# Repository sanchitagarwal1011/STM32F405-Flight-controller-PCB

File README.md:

# STM32F405 Flight Controller PCB

A custom flight controller PCB designed in KiCad 10 using the STM32F405 microcontroller.

This project focuses on embedded systems, PCB design, and drone electronics.

## Project Overview

The board includes:

- STM32F405 microcontroller
- ICM-20602 6-axis IMU
- BMP280 barometric pressure sensor
- AMS1117-3.3 voltage regulator
- USB interface
- ESC signal connections
- RC receiver connections
- Reset and boot controls
- Power filtering and decoupling capacitors

## Tools Used

- KiCad 10
- Embedded C
- Git
- GitHub

## PCB Design

### Schematic

### PCB Layout

### 3D View

## Design Features

- STM32F405-based flight controller
- Dedicated ground plane
- Separate power and signal routing
- Decoupling capacitors near IC power pins
- IMU placed close to the microcontroller
- Power filtering for sensitive components
- Design-rule checking using KiCad

## Project Status

- [x] Schematic design
- [x] Component selection
- [x] Footprint assignment
- [x] PCB placement
- [x] PCB routing
- [x] Ground-zone filling
- [x] Design-rule checking
- [x] Gerber generation
- [ ] PCB manufacturing
- [ ] Hardware testing

## Reference

This project is inspired by PCB design learning material from Phil’s Lab.

## Disclaimer

This is a learning and development project. The board has not yet been flight-tested and should not be used in a real drone.

## Author

Sanchit Agarwal

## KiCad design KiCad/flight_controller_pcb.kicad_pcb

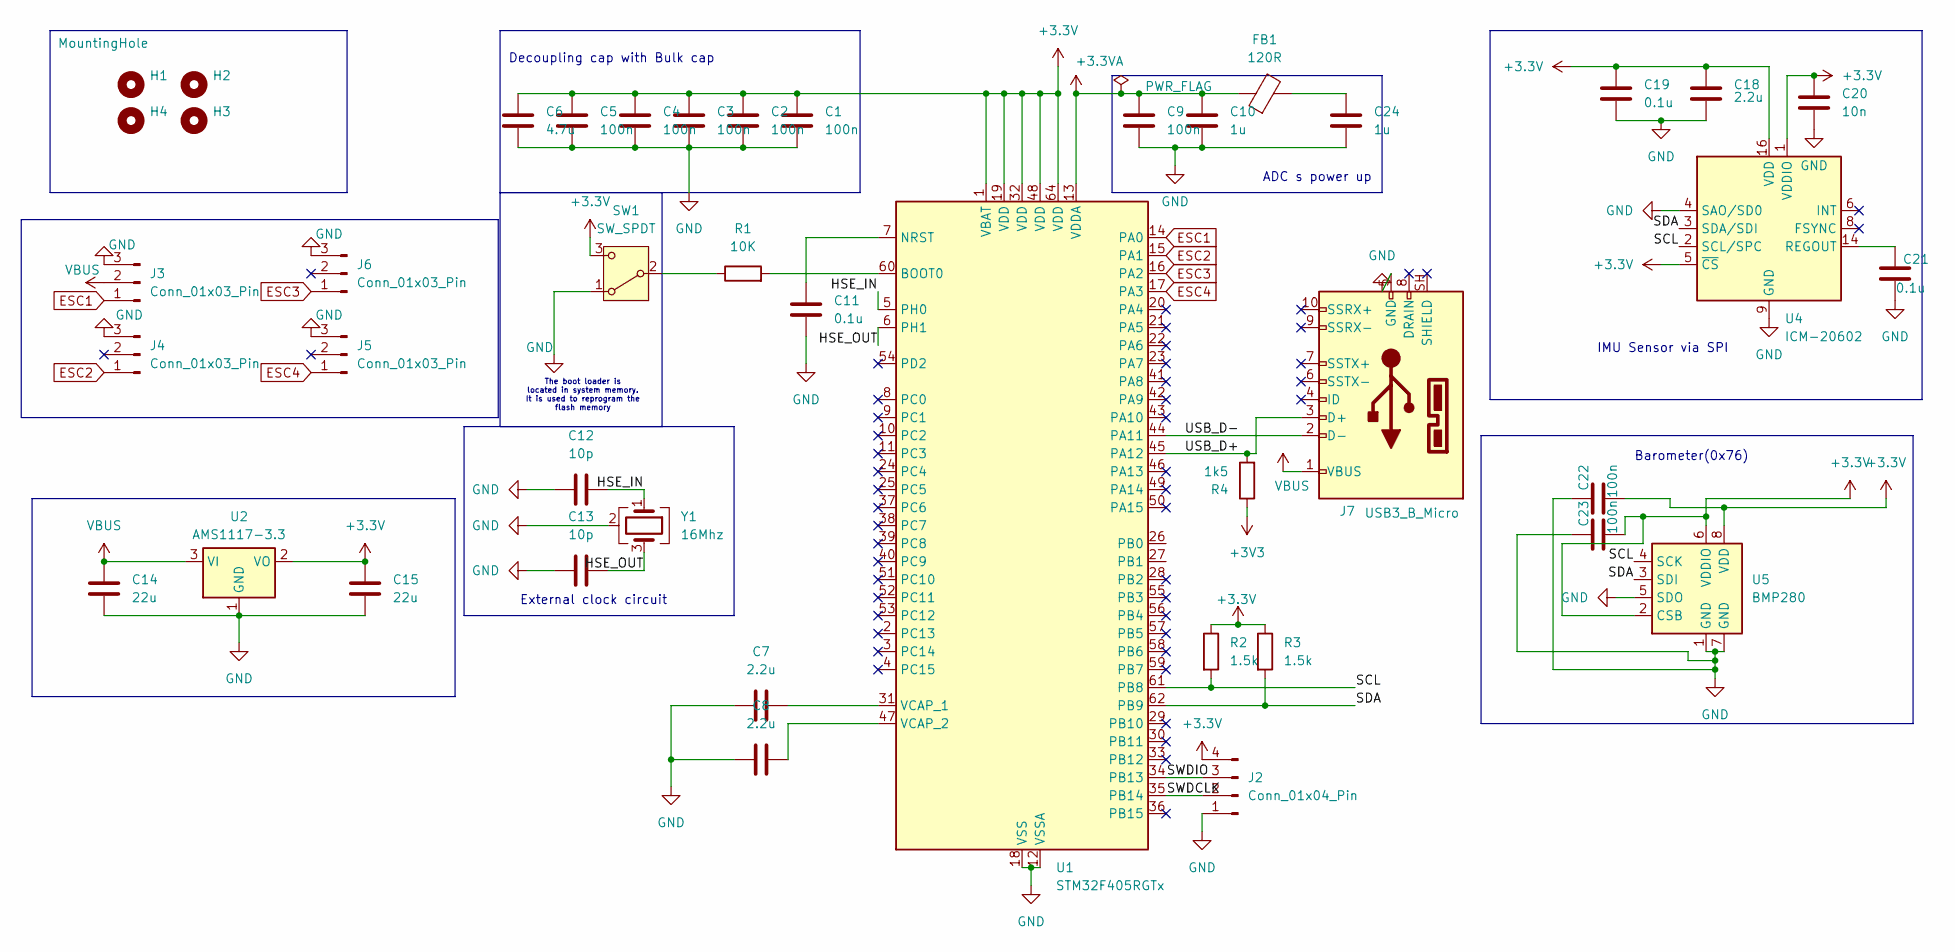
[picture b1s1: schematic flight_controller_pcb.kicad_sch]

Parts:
C1, C2, C3, C4, C5, C9, C22, C23: 100n; C_0603_1608Metric
C6: 4.7u; C_0603_1608Metric
C7, C8: 2.2u; C_0805_2012Metric
C10, C24: 1u; C_0603_1608Metric
C11, C19, C21: 0.1u; C_0603_1608Metric
C12, C13: 10p; C_0603_1608Metric
C14, C15: 22u; C_0805_2012Metric
C18: 2.2u; C_0603_1608Metric
C20: 10n; C_0603_1608Metric
FB1: 120R; L_0603_1608Metric
H1, H2, H3, H4: MountingHole; MountingHole_2.1mm
J2: Conn_01x04_Pin; PinHeader_1x04_P2.54mm_Vertical
J3, J4, J5, J6: Conn_01x03_Pin; PinHeader_1x03_P2.54mm_Vertical
J7: USB3_B_Micro; USB_Micro-B_Wuerth_629105150521
R1: 10K; R_0805_2012Metric
R2, R3: 1.5k; R_0805_2012Metric
R4: 1k5; R_0402_1005Metric
SW1: SW_SPDT; SW_SPDT_PCM12
U1: STM32F405RGTx; LQFP-64_10x10mm_P0.5mm
U2: AMS1117-3.3; SOT-223-3_TabPin2
U4: ICM-20602; LGA-16_3x3mm_P0.5mm_LayoutBorder3x5y
U5: BMP280; Bosch_LGA-8_2x2.5mm_P0.65mm_ClockwisePinNumbering
Y1: 16Mhz; Crystal_SMD_3225-4Pin_3.2x2.5mm

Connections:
+3.3V: C1.1, C2.1, C3.1, C4.1, C5.1, C6.1, C15.1, C18.1, C19.1, C20.1, C22.2, C23.2, J2.4, R2.1, R3.1, SW1.3 (C), U1.1 (VBAT), U1.19 (VDD), U1.32 (VDD), U1.48 (VDD), U1.64 (VDD), U2.2 (VO), U4.1 (VDDIO), U4.5 (~CS), U4.16 (VDD), U5.2 (CSB), U5.6 (VDDIO), U5.8 (VDD)
+3.3VA: C9.1, C10.1, FB1.1, U1.13 (VDDA)
+3V3: R4.1
/HSE_IN: C12.1, U1.5 (PH0), Y1.1
/HSE_OUT: C13.1, U1.6 (PH1), Y1.3
/SCL: R2.2, U1.61 (PB8), U4.2 (SCL/SPC), U5.4 (SCK)
/SDA: R3.2, U1.62 (PB9), U4.3 (SDA/SDI), U5.3 (SDI)
/SWDCLK: J2.2, U1.35 (PB14)
/SWDIO: J2.3, U1.34 (PB13)
/USB_D+: J7.3 (D+), R4.2, U1.45 (PA12)
/USB_D-: J7.2 (D-), U1.44 (PA11)
ESC1: J3.1, U1.14 (PA0)
ESC2: J4.1, U1.15 (PA1)
ESC3: J6.1, U1.16 (PA2)
ESC4: J5.1, U1.17 (PA3)
GND: C1.2, C2.2, C3.2, C4.2, C5.2, C6.2, C7.2, C8.1, C9.2, C10.2, C11.2, C12.2, C13.2, C14.2, C15.2, C18.2, C19.2, C20.2, C21.2, C22.1, C23.1, C24.2, J2.1, J3.3, J4.3, J5.3, J6.3, J7.5 (GND), SW1.1 (A), U1.12 (VSSA), U1.18 (VSS), U1.63 (VSS), U2.1 (GND), U4.4 (SAO/SD0), U4.9 (GND), U4.10 (GND), U4.11 (GND), U4.12 (GND), U4.13 (GND), U4.15 (GND), U5.1 (GND), U5.5 (SDO), U5.7 (GND), Y1.2 (G), Y1.4 (G)
unnamed: C24.1, FB1.2
unnamed: R1.1, SW1.2 (B)
unnamed: R1.2, U1.60 (BOOT0)
unnamed: C11.1, U1.7 (NRST)
unnamed: C7.1, U1.31 (VCAP_1)
unnamed: C8.2, U1.47 (VCAP_2)
unnamed: C21.1, U4.14 (REGOUT)
VBUS: C14.1, J3.2, J7.1 (VBUS), U2.3 (VI)

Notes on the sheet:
ADC s power up
External clock circuit
Barometer(0x76)
IMU Sensor via SPI
Decoupling cap with Bulk cap
The boot loader is located in system memory. It is used to reprogram the flash memory

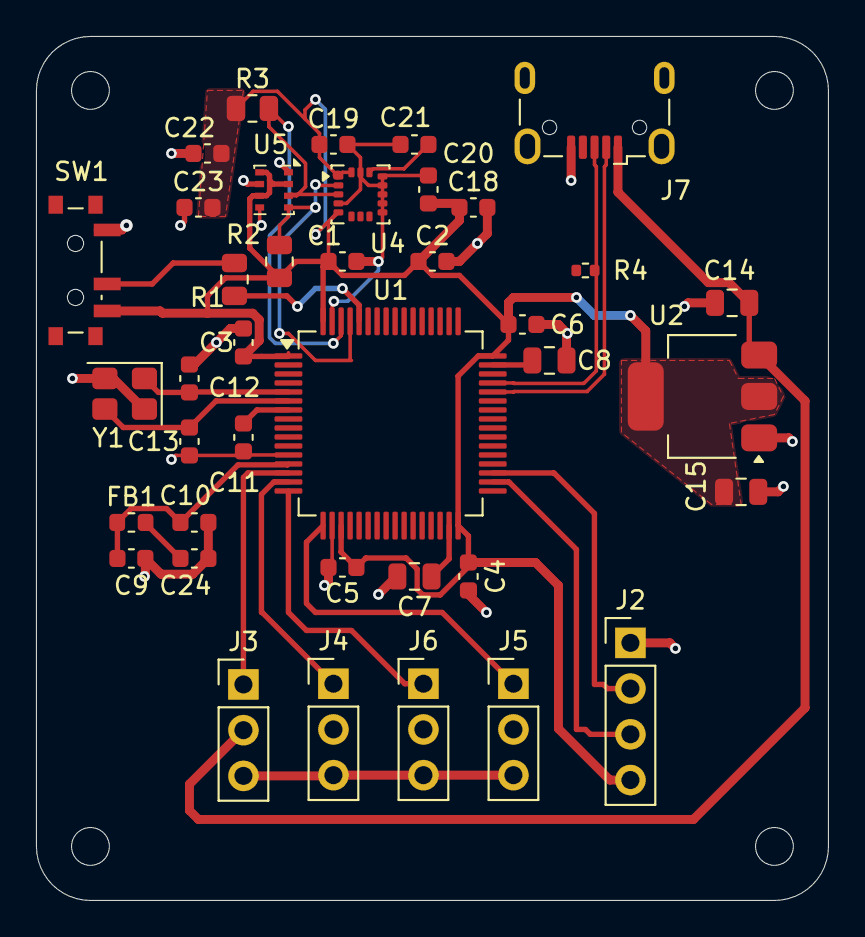
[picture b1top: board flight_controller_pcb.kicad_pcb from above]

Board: 2 copper layers, 44.0 x 48.0 mm, 43 parts (0 on the bottom side), 23 nets.

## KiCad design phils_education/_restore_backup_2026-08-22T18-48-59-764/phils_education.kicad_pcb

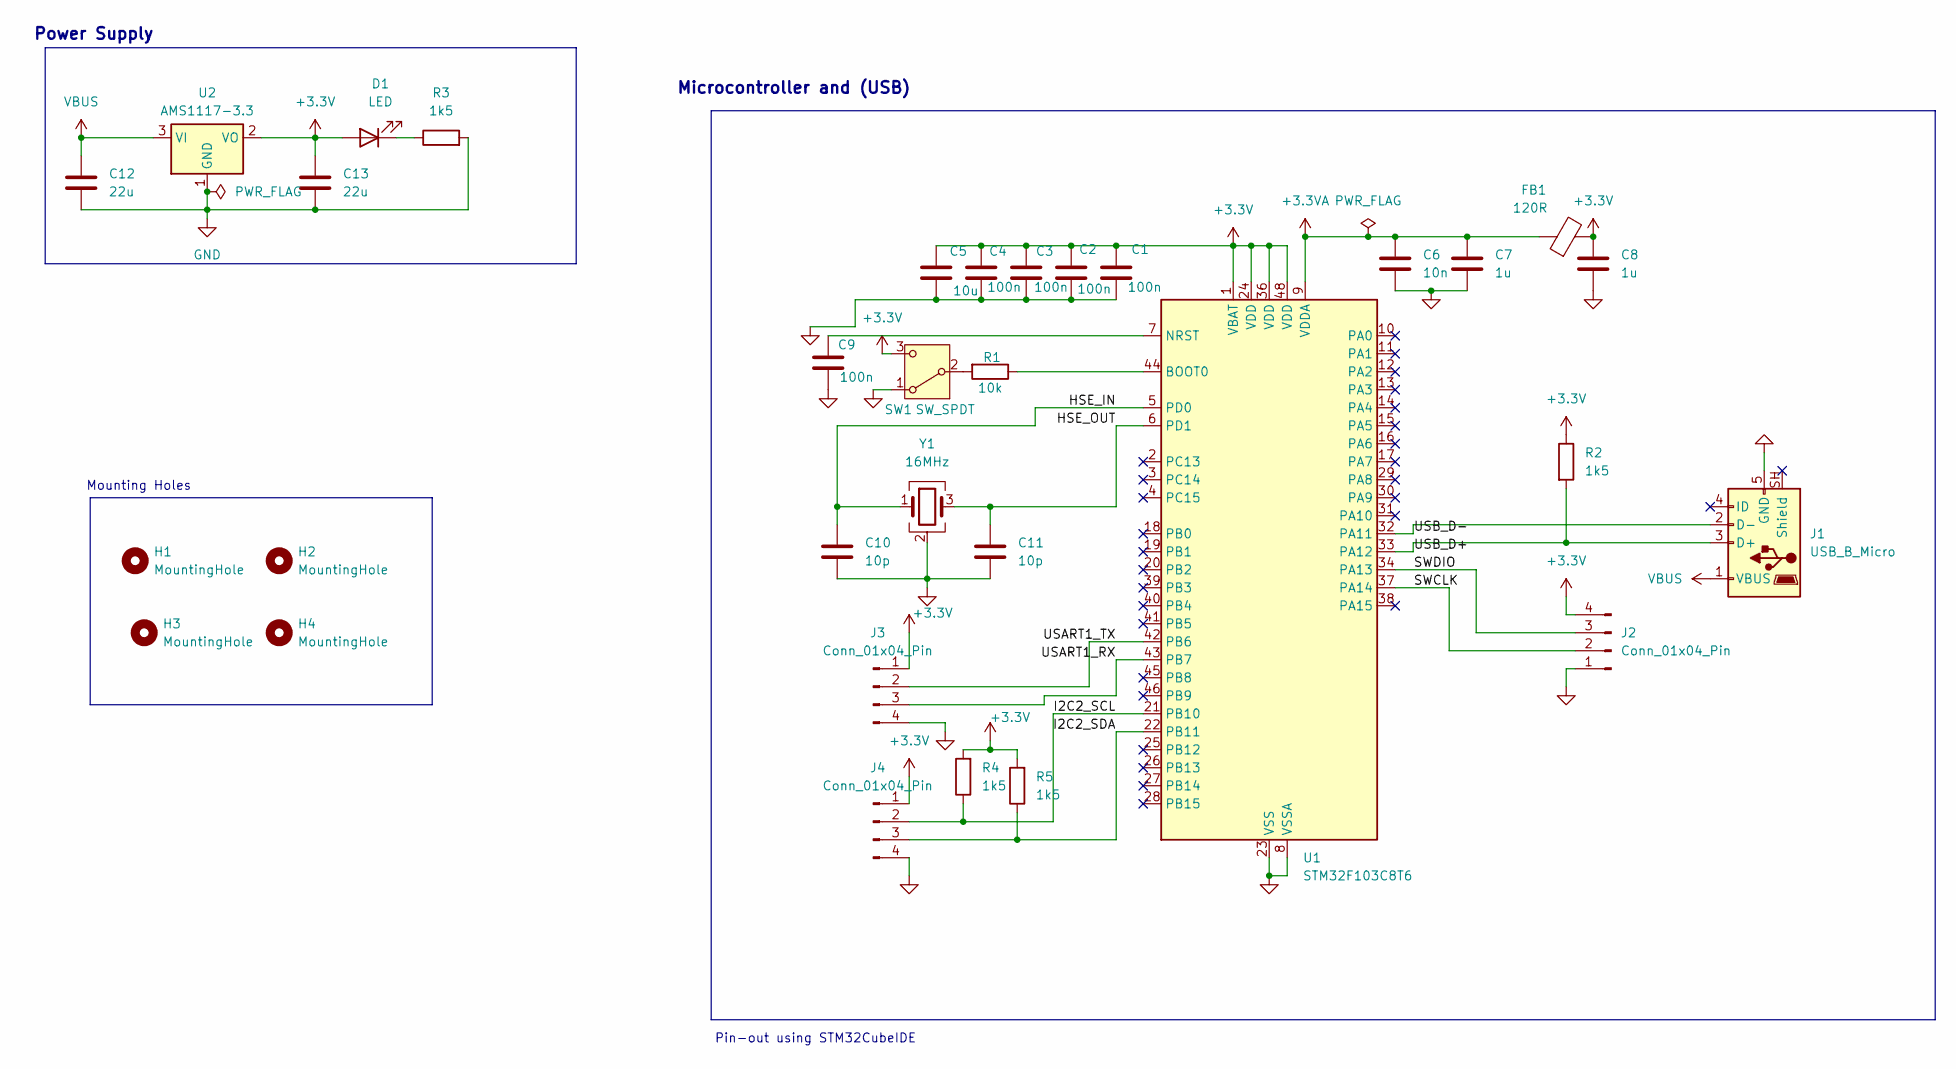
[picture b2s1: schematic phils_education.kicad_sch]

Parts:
C1, C2, C3, C4, C9: 100n; C_0402_1005Metric
C5: 10u; C_0603_1608Metric
C6: 10n; C_0603_1608Metric
C7, C8: 1u; C_0402_1005Metric
C10, C11: 10p; C_0402_1005Metric
C12, C13: 22u; C_0805_2012Metric
D1: LED; LED_0603_1608Metric
FB1: 120R; L_0603_1608Metric
H1, H2, H3, H4: MountingHole; MountingHole_2.2mm_M2
J1: USB_B_Micro; USB_Micro-B_Wuerth_614105150721_Vertical
J2, J3, J4: Conn_01x04_Pin; PinHeader_1x04_P2.54mm_Vertical
R1: 10k; R_0402_1005Metric
R2, R3, R4, R5: 1k5; R_0402_1005Metric
SW1: SW_SPDT; SW_SPST_B3U-1100P
U1: STM32F103C8T6; LQFP-48_7x7mm_P0.5mm
U2: AMS1117-3.3; SOT-223-3_TabPin2
Y1: 16MHz; Crystal_SMD_3225-4Pin_3.2x2.5mm

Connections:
+3.3V: C1.1, C2.1, C3.1, C4.1, C5.1, C8.1, C13.1, D1.2 (A), FB1.2, J2.4, J3.1, J4.1, R2.1, R4.2, R5.2, SW1.3 (C), U1.1 (VBAT), U1.24 (VDD), U1.36 (VDD), U1.48 (VDD), U2.2 (VO)
+3.3VA: C6.1, C7.1, FB1.1, U1.9 (VDDA)
/HSE_IN: C10.1, U1.5 (PD0), Y1.1
/HSE_OUT: C11.1, U1.6 (PD1), Y1.3
/I2C2_SCL: J4.2, R4.1, U1.21 (PB10)
/I2C2_SDA: J4.3, R5.1, U1.22 (PB11)
/SWCLK: J2.2, U1.37 (PA14)
/SWDIO: J2.3, U1.34 (PA13)
/USART1_RX: J3.3, U1.43 (PB7)
/USART1_TX: J3.2, U1.42 (PB6)
/USB_D+: J1.3 (D+), R2.2, U1.33 (PA12)
/USB_D-: J1.2 (D-), U1.32 (PA11)
<NO NET>: C1.2, C2.2, C3.2, C4.2, C5.2, C6.2, C7.2, C8.2, J1.5 (GND), J2.1, J3.4, J4.4, U1.8 (VSSA), U1.23 (VSS), U1.35 (VSS), U1.47 (VSS)
GND: C9.2, C10.2, C11.2, C12.2, C13.2, R3.2, SW1.1 (A), U2.1 (GND), Y1.2 (G), Y1.4 (G)
unnamed: D1.1 (K), R3.1
unnamed: R1.2, SW1.2 (B)
unnamed: R1.1, U1.44 (BOOT0)
unnamed: C9.1, U1.7 (NRST)
VBUS: C12.1, J1.1 (VBUS), U2.3 (VI)

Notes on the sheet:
Power Supply
Mounting Holes
Pin-out using STM32CubeIDE
Microcontroller and (USB)

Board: 2 copper layers, 32 parts (0 on the bottom side), 19 nets, no tracks yet.
